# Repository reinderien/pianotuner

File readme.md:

# Custom Piano Tuner

## Environment

### apt packages

- libasound2-dev (for compilation only)
- libasound2 - underlying ALSA support
- linux-libc-dev - Linux headers for SPI

Remove pulseaudio.

Todo: move to headless mode and blow away a pile of unneeded packages.

### /boot/config.txt

```
# See https://rpf.io/configtxt
dtparam=spi=on

dtoverlay=spi0-1cs

arm_64bit=1

# todo: turn off video
```

### Audio USB device details

`dmesg`:

```
usb 1-1.2: new full-speed USB device number 3 using xhci_hcd
usb 1-1.2: New USB device found, idVendor=0d8c, idProduct=013c, bcdDevice= 1.00
usb 1-1.2: New USB device strings: Mfr=1, Product=2, SerialNumber=0
usb 1-1.2: Product: USB PnP Sound Device
usb 1-1.2: Manufacturer: C-Media Electronics Inc.      
input: C-Media Electronics Inc.       USB PnP Sound Device as /devices/platform/scb/fd500000.pcie/pci0000:00/0000:00:00.0/0000:01:00.0/usb1/1-1/1-1.2/1-1.2:1.2/0003:0D8C:013C.0001/input/input0
hid-generic 0003:0D8C:013C.0001: input,hidraw0: USB HID v1.00 Device [C-Media Electronics Inc.       USB PnP Sound Device] on usb-0000:01:00.0-1.2/input2
```

`lsusb`:

```
Bus 001 Device 003: ID 0d8c:013c C-Media Electronics, Inc. CM108 Audio Controller
```

`arecord -l`:

```
**** List of CAPTURE Hardware Devices ****
card 1: Device [USB PnP Sound Device], device 0: USB Audio [USB Audio]
  Subdevices: 1/1
  Subdevice #0: subdevice #0
```

`arecord -L`:

```
default:CARD=Device
    USB PnP Sound Device, USB Audio
    Default Audio Device
sysdefault:CARD=Device
    USB PnP Sound Device, USB Audio
    Default Audio Device
hw:CARD=Device,DEV=0
    USB PnP Sound Device, USB Audio
    Direct hardware device without any conversions
plughw:CARD=Device,DEV=0
    USB PnP Sound Device, USB Audio
    Hardware device with all software conversions
```

Examine these lines in `/usr/share/alsa/alsa.conf`; the defaults should
correspond to the correct card and device listed above:

```
defaults.ctl.card 1
defaults.pcm.card 1
defaults.pcm.device 0
defaults.pcm.subdevice 0
```

### Audio input test

```
$ arecord -D hw:CARD=Device,DEV=0 -c 1 -f S16_LE -r 48000 -d 1 -v output-test
Recording WAVE 'output-test' : Signed 16 bit Little Endian, Rate 48000 Hz, Mono
Hardware PCM card 2 'USB PnP Sound Device' device 0 subdevice 0
Its setup is:
  stream       : CAPTURE
  access       : RW_INTERLEAVED
  format       : S16_LE
  subformat    : STD
  channels     : 1
  rate         : 48000
  exact rate   : 48000 (48000/1)
  msbits       : 16
  buffer_size  : 24000
  period_size  : 6000
  period_time  : 125000
  tstamp_mode  : NONE
  tstamp_type  : MONOTONIC
  period_step  : 1
  avail_min    : 6000
  period_event : 0
  start_threshold  : 1
  stop_threshold   : 24000
  silence_threshold: 0
  silence_size : 0
  boundary     : 1572864000
  appl_ptr     : 0
  hw_ptr       : 0
```

### Verifying SPI

```
$ raspi-gpio get | grep SPI0
GPIO 9: level=0 fsel=4 alt=0 func=SPI0_MISO pull=DOWN
GPIO 10: level=0 fsel=4 alt=0 func=SPI0_MOSI pull=DOWN
GPIO 11: level=0 fsel=4 alt=0 func=SPI0_SCLK pull=DOWN
```

```
$ lsmod | grep spi
spidev                 24576  0
spi_bcm2835            24576  0
```

```
$ ls -l /dev/spi*
crw-rw---- 1 root spi 153, 0 Dec  5 17:06 /dev/spidev0.0
```

```
# First, guarantee sync; this requires at most two bytes
echo -ne "\x00\x00" > /dev/spidev0.0

# Channel 1: 1V, 205: 0b001_000_00 0b1100_1101
echo -ne "\x20\xCD" > /dev/spidev0.0

# Channel 2: 2V, 410: 0b010_000_01 0b1001_1010
echo -ne "\x41\x9A" > /dev/spidev0.0

# Channel 5: 3V, 614: 0b101_000_10 0b0110_0110
echo -ne "\xA2\x66" > /dev/spidev0.0

# Channel 4: 4V, 26, 0b100_11001
echo -ne "\x99" > /dev/spidev0.0
```

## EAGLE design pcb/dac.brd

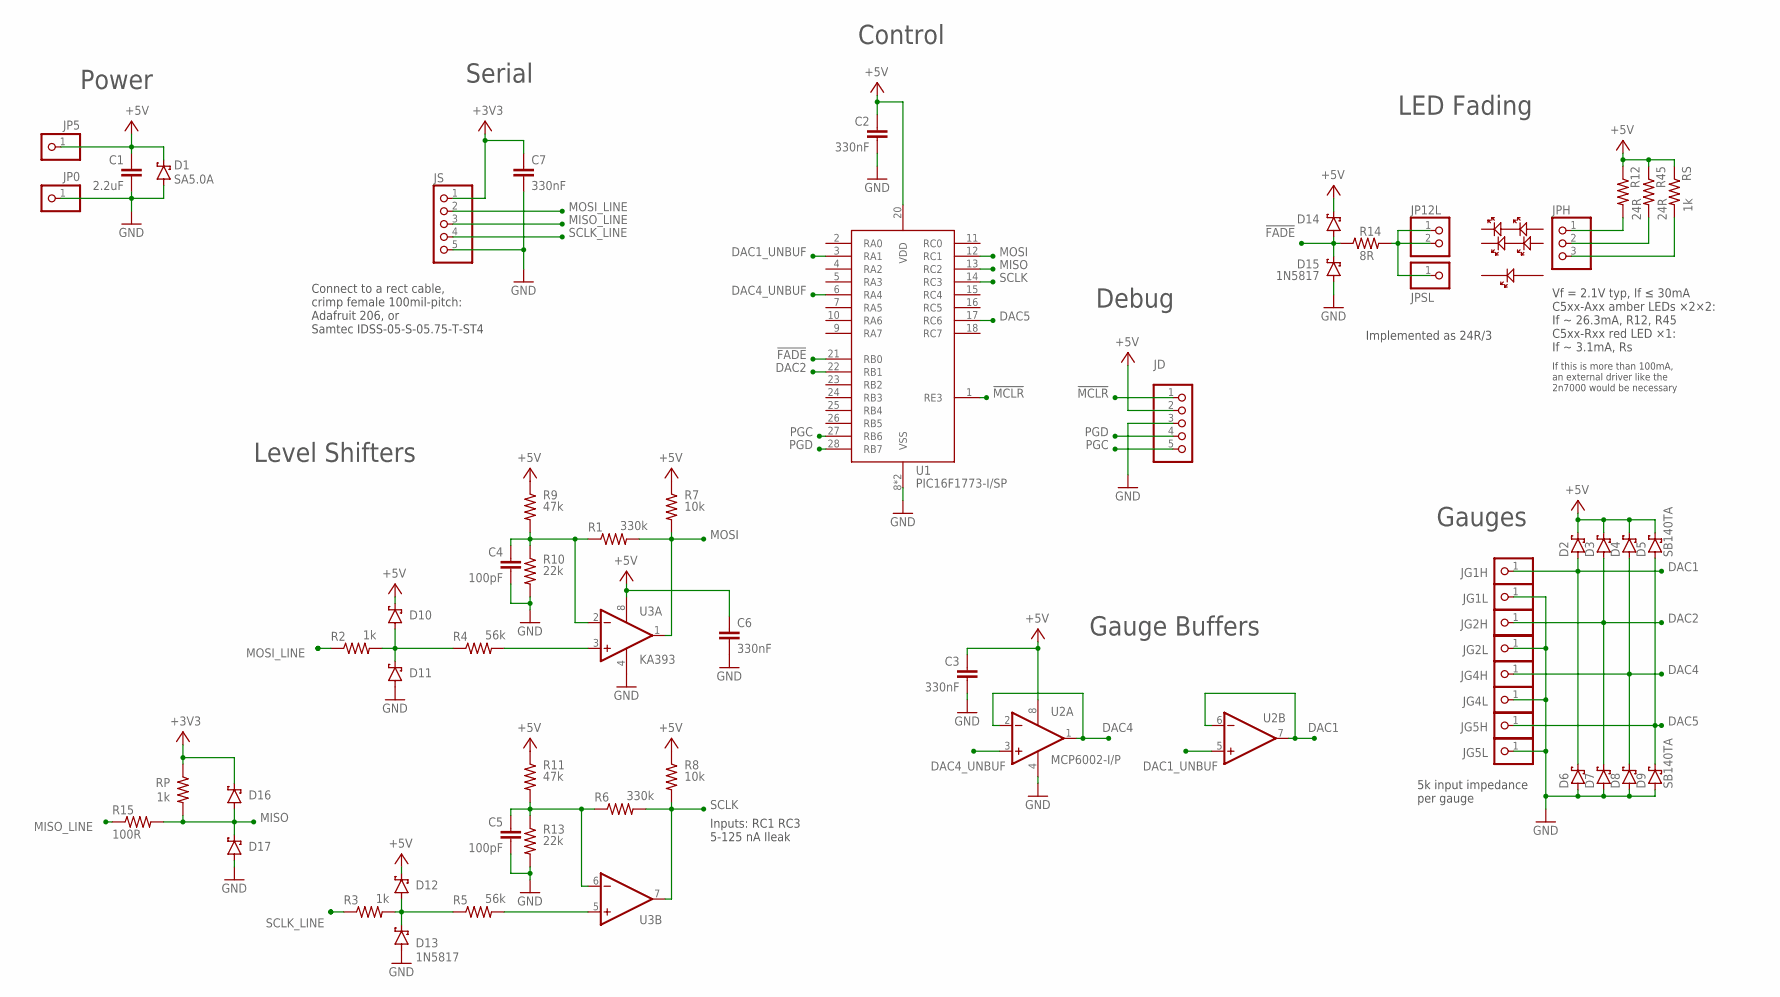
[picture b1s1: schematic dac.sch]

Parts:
C1: 2.2uF; C050-024X044
C2, C3, C6, C7: 330nF; C050-024X044
C4, C5: 100pF; C050-024X044
D1: SA5.0A; ZDIO-2.5
D2, D3, D4, D5, D6, D7, D8, D9: SB140TA; DO41-7.6
D10: 1N5817-H76; DO41-7.6
D11: 1N5817-V; ZDIO-2.5
D12, D16, D17: 1N5817-T; DO41-7.6
D13: 1N5817; DO41-10
D14, D15: 1N5817; ZDIO-2.5
JD: PINHD-1X5; 1X05
JG1H, JG1L, JG2H, JG2L, JG4H, JG4L, JG5H, JG5L: PINHD-1X1; 1X01
JP0, JP5: PINHD-1X1; 1X01
JP12L: PINHD-1X2; 1X02
JPH: PINHD-1X3; 1X03
JPSL: PINHD-1X1; 1X01
JS: PINHD-1X5; 1X05
R1, R6: 330k; 0207/2V
R2: 1k; 0204/7
R3: 1k; 0207/10
R4: 56k; 0207/10
R5: 56k; 0207/12
R7, R8: 10k; 0207/2V
R9: 47k; 0207/7
R10, R13: 22k; 0207/5V
R11: 47k; 0207/5V
R12, R45: 24R; 0207/2V
R14: 8R; 0207/15
R15: 100R; 0207/10
RP: 1k; 0207/5V
RS: 1k; 0207/2V
U1: PIC16F1773-I/SP; DIL28-3
U2: MCP6002-I/P; DIL08
U3: KA393; DIL08

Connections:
!FADE: D14.A, D15.C, R14.1, U1.21 (RB0)
!FADE_PROT: JP12L.1, JP12L.2, JPSL.1, R14.2
!MCLR: JD.1, U1.1 (RE3)
+3V3: C7.1, D16.C, JS.1, RP.1
+5V: C1.1, C2.1, C3.1, C6.1, D1.C, D2.C, D3.C, D4.C, D5.C, D10.C, D12.C, D14.C, JD.2, JP5.1, R7.1, R8.1, R9.1, R11.1, R12.1, R45.1, RS.1, U1.20 (VDD), U2.8 (V+), U3.8 (V+)
DAC1: D2.A, D6.C, JG1H.1, U2.6 (-IN), U2.7 (OUT)
DAC1_UNBUF: U1.3 (RA1), U2.5 (+IN)
DAC2: D3.A, D7.C, JG2H.1, U1.22 (RB1)
DAC4: D4.A, D8.C, JG4H.1, U2.1 (OUT), U2.2 (-IN)
DAC4_UNBUF: U1.6 (RA4), U2.3 (+IN)
DAC5: D5.A, D9.C, JG5H.1, U1.17 (RC6)
GND: C1.2, C2.2, C3.2, C4.2, C5.2, C6.2, C7.2, D1.A, D6.A, D7.A, D8.A, D9.A, D11.A, D13.A, D15.A, D17.A, JD.3, JG1L.1, JG2L.1, JG4L.1, JG5L.1, JP0.1, JS.5, R10.2, R13.2, U1.8 (VSS), U1.19 (VSS), U2.4 (V-), U3.4 (V-)
LED1: JPH.1, R12.2
LED2: JPH.2, R45.2
LEDSUP: JPH.3, RS.2
MISO: D16.A, D17.C, R15.2, RP.2, U1.13 (RC2)
MISO_LINE: JS.3, R15.1
MOSI: R1.2, R7.2, U1.12 (RC1), U3.1 (OUT)
MOSI_LINE: JS.2, R2.1
MOSI_N: C4.1, R1.1, R9.2, R10.1, U3.2 (-IN)
MOSI_P: R4.2, U3.3 (+IN)
MOSI_PROT: D10.A, D11.C, R2.2, R4.1
PGC: JD.5, U1.27 (RB6)
PGD: JD.4, U1.28 (RB7)
SCLK: R6.2, R8.2, U1.14 (RC3), U3.7 (OUT)
SCLK_LINE: JS.4, R3.1
SCLK_N: C5.1, R6.1, R11.2, R13.1, U3.6 (-IN)
SCLK_P: R5.2, U3.5 (+IN)
SCLK_PROT: D12.A, D13.C, R3.2, R5.1

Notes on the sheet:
5k input impedance per gauge
Connect to a rect cable, crimp female 100mil-pitch: Adafruit 206, or Samtec IDSS-05-S-05.75-T-ST4
Vf = 2.1V typ, If ≤ 30mA C5xx-Axx amber LEDs ×2×2: If ~ 26.3mA, R12, R45 C5xx-Rxx red LED ×1: If ~ 3.1mA, Rs
Gauges
Gauge Buffers
LED Fading
Serial
Debug
Power
Control
If this is more than 100mA, an external driver like the 2n7000 would be necessary
Inputs: RC1 RC3 5-125 nA Ileak
Level Shifters
Implemented as 24R/3

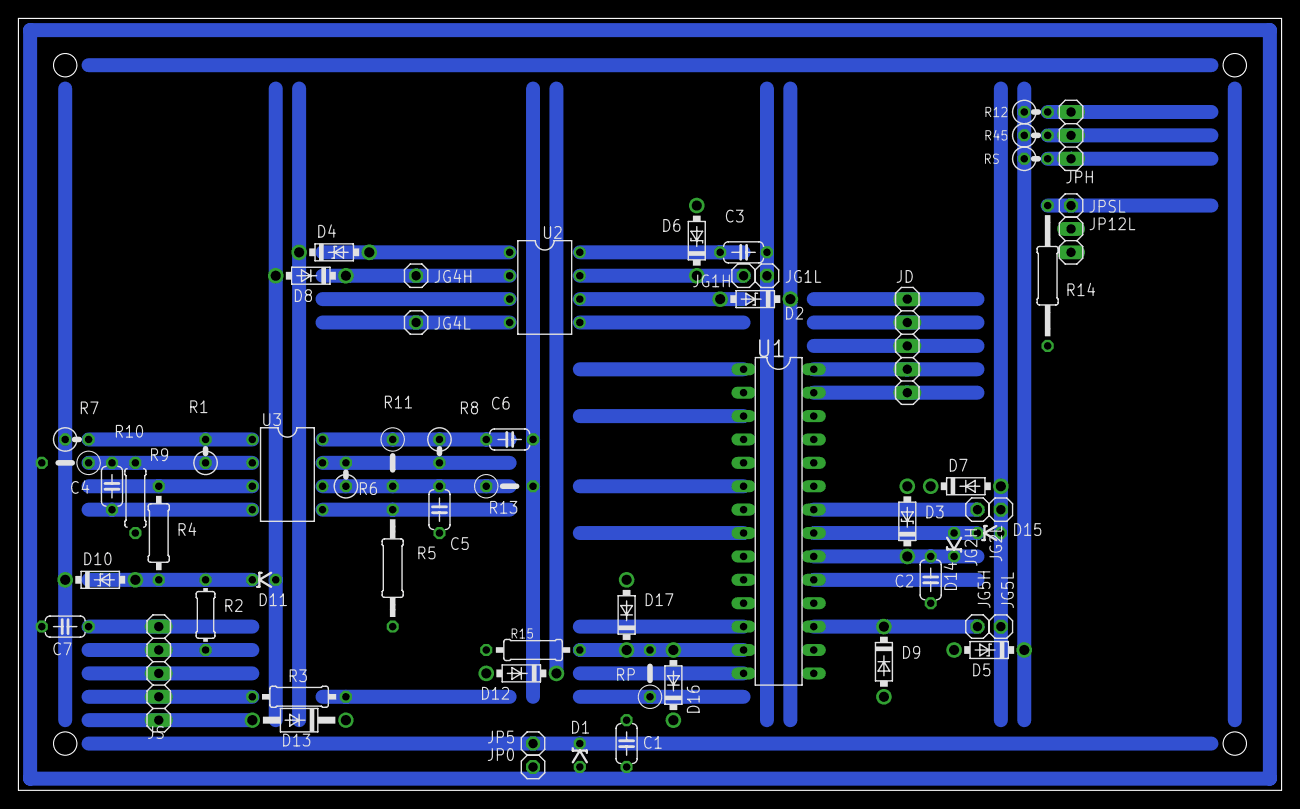
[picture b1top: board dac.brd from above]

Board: 2 copper layers, 137.2 x 83.8 mm, 60 parts (0 on the bottom side), 29 nets.

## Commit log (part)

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2015-12-20 Initial commit - successfully captures and plots
2015-12-20 Note detection
2015-12-20 Interpolate for graphing
2015-12-20 Move capture callback out to top level
2015-12-21 Working updating graph
2015-12-21 Tuning subplot
2020-10-03 Move ancient Python script to a subdirectory
2020-10-04 SDL capture (uses Alsa underneath)
2020-10-04 Rely on git for clean
2020-10-04 Output flags before build
2020-10-05 Switch to ALSA
2020-10-05 Some hardware parameter selection
2020-10-05 Drop trailing spaces; apply the hwparams
2020-10-05 Use ALSA dump feature
2020-10-05 Show skip-messages in enumeration
2020-10-05 Parametric gcc
2020-10-05 Warnings while shutting down pcm
2020-10-05 Explicitly include device number in pcm open call
2020-10-05 Explicitly reference subdevice in name; fix alloca bug
2020-10-06 Do some calculations; move to a minimum permissible sampling freq
2020-10-06 Basic capture runs
2020-10-06 Qualify some context pointers
2020-10-06 Do an initial start to avoid a first restart bump
2020-10-06 Add a control info section
2020-10-06 Describe elements
2020-10-06 Array-ize more name utilities
2020-10-06 Add sanity checks for enums
2020-10-06 Show current element values
2020-10-06 Modify AGC and gain
2020-10-06 Infinite loop; catch sigint; basic monitor
2020-10-06 Fix the double free
2020-10-07 Base volume on a fraction of max
2020-10-07 Those constants are all for open
2020-10-07 Do not care about min
2020-10-10 Basic GSL build
2020-10-10 Wrong headers for readme
2020-10-10 Greatly simplify makefile; fix Atlas include order
2020-10-10 Don't care about gcc location
2020-10-11 Support debug/release profile
2020-10-11 Reduce default verbosity of element dump
2020-10-11 Initialize max_int, though it will not matter in our case
2020-10-11 Split off frequency analysis
2020-10-11 Split out meter and dump routines
2020-10-11 Initial notes on BLAS
2020-10-12 Use default device instead of enumerating; float conversion yields all 0 so far
2020-10-12 Switch back to mmap s16; try out some BLAS which does not work
2020-10-12 Trial implementation using dot products
2020-10-12 Dot product method seems to work, 4ms
2020-10-12 Dump GSL
2020-10-12 Move to cblas notes
2020-10-12 Show frequency in dump
2020-10-12 Parametric rate
2020-10-12 Valley-to-peak algorithm
2020-10-12 Finding good thresholds is going to be tricky
2020-10-12 This space hack has to go
2020-10-12 Next is a calibration aide
2020-10-19 Empty PIC project
2020-10-20 Basic assembling, link and program
2020-10-20 Only init once
2020-10-21 Do a bunch of PIC init
2020-10-21 PPS, SPI and opamp init
2020-10-23 Initial schematic for DAC
2020-10-23 start a journal retroactively
2020-10-23 Switch to high-voltage programming
2020-10-23 More journal details - including reference to the old Google doc
2020-10-23 Some pics for the journal; not yet embedded
2020-10-23 Embed pictures and descriptions in journal
2020-10-23 Supplier correction
2020-10-25 Notes from Oct 24 on fade subprogram
2020-10-28 Yet more fade calculations
2020-10-30 Add fade circuit and a little firmware
2020-10-30 Start timer 2
2020-11-01 Simultaneous start
2020-11-24 PWM beat frequency works great; COG has trouble somehow related to input PWM duty cycle
2020-11-25 Fade works
2020-11-25 Fade-in complete - timer interrupt works
2020-11-25 Add image of fading test circuit
2020-11-26 Terminology
2020-11-26 Increase LED drive current to 13mA
2020-11-27 Protoboard layout & routing
2020-11-27 Journal entry for DAC layout
2020-11-29 Add an (untested) implementation for SPI receiver
2020-12-01 Offset null calculations
2020-12-05 Journal - SPI stuff
2020-12-05 Notes on diffusion angle and lighting
2020-12-06 Start a gauge file; drag ALSA back to working
2020-12-06 Bash test; not working on scope yet
2020-12-06 Draft SPI parent code; will not compile yet
2020-12-06 Compilation for SPI cleaned up
2020-12-07 Level shifting for Pi
2020-12-07 Continue if xor IS zero
2020-12-13 Fix up the likely source of the MSSP problem
2020-12-13 Journal entry for woodworking
2020-12-13 MISO pullup, minor cleanup
2020-12-13 Fix polarity of MSSP
2020-12-13 Add note about high driving
2020-12-13 Simulation of SPI clock Schmitt trigger
2020-12-18 Only sleep before first byte; works at 1MHz
2020-12-18 Gauge demo
2020-12-18 Fix seconds issue
2020-12-18 Disable watchdog for now
2020-12-18 Journal entry for 17th
2020-12-19 Drop FET driver for LEDs; switch to HIDRV on B0 in open-drain mode; LEDs in serial
2020-12-19 Get closer to 30mA based on a parallel approximation; parts on hand and whatnot
2020-12-20 Journal entry for the 19th
2020-12-21 Ended up using 1k for power indicator; journal entry
2020-12-22 Journal images for gauges and math notes
2020-12-22 Journal entry for the 22nd
2020-12-30 Holiday journal entry
2020-12-31 Refactoring pass; currently segfaults in matplotlib draw
2021-01-11 Re-vamp the desktop spectral analysis - running, now needs tuning view
2021-01-11 Fundamental A440 in cents
2021-01-11 Wisdom recovery, max-normalisation
2021-01-11 Multi-harmonic display shown
2021-01-11 Halfway through adding keyboard support, classify
2021-01-11 Initial note, wisdom logic fix
2021-01-11 Everything basically works
2021-01-11 Replaced all tabs with four spaces.
2021-01-11 Added mod1rd_test and vrb_test to arm/.gitignore.
2021-01-11 A first volley at reimplementing the frequency determination code.
    - Autocorrelation is now time-averaged using a VRB.
    - Nuked the old, mostly broken frequency determination code.
    - The audio capture history and autocorrelation accumulation are now managed in
    main.c. The main peak finding still occurs in freq.c. The autocorrelation
    array and sample rate are passed as inputs.
    - Autocorrelation snapshots are now saved in raw binary format. (It is actually
2021-01-11 Implemented the Virtual Ring Buffer, plus unit tests.
    It isn't a FIFO implementation, with enqueuing and dequeuing. Its purpose is
    to store the history of a stream so that any point a certain distance in the
    past or later can be accessed. It still has what is an equivalent to enqueuing,
    called advance. It also has a "past" method, for controlled access to the
    stream's past.
2021-01-11 Switched to armpl.
2021-01-11 stropts.h is deprecated. Switching to sys/ioctl.h.
2021-01-11 Added statefulness to consume() and frequency determination code, preliminary gauge value calculation code.
    Also, removed dependency on freq.h in the audio capture code. The capture
    period is now determined by a hardcoded latency. Any history that needs to be
    captured and tracked will be done so in a separate ring buffer.
2021-01-11 Turned on gauges, fixed a db<->octave mixup, adjusted POWER_THRESHOLD.
2021-01-11 Nuke MIN_LATENCY, miscellaneous cosmetics.
2021-01-11 Resolved some double gauge message sends in the state code.
2021-01-12 Saner slicing
2021-01-13 Enforce max note, add frequency display
2021-04-29 Diffused backlights
2021-04-29 That is not a bullet
2021-06-06 Do not sleep if we are out of sync
2021-06-17 Micro issue fixup, H3s for dates
2022-05-08 Update toolchain (historical)
2022-05-08 Informative labels (historical)
2022-05-08 Update pack
2022-05-08 Enable the watchdog
2024-03-31 Some manual watchdog diagnostics
2024-03-31 Remove bogus line
2024-06-01 First stab at a numerical solution to level shifter
2024-06-01 Temporarily cut out alternative parameter structures
2024-06-02 Close to a working differential_evolution sol
2024-06-02 Callback output
2024-06-02 Add bias current
2024-06-03 Add vectorisation
2024-06-03 Add continuous printing
2024-06-03 Journal entries for level shifter
2024-06-03 Add bias to high case; add pullup constraint
2024-06-30 Add more examples
2024-07-01 New layout with larger board and level shifter
2024-07-01 Final modifications to level_shifter - restore support for continuous case
2024-07-01 MISO protection network, lower capacitance values, split jumper for LEDs
2024-07-01 Replace screw terminals with more header
2024-07-01 Update pack to 1.7.242. Add debug and release configurations. Add preliminary support for psect optimisation flags. Add comments on bank values. Convert to WPU for unused inputs. ST input levels thro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
2024-07-01 Switch back from simulator to PICkit
2024-07-01 Switch to analogue for unused pins
2024-08-04 Used different protection diodes for LEDs
2024-08-05 Do not pull MISO to 5V
2024-08-10 Modernise typing
2024-08-10 More typing
2026-06-14 Halfway through a rewrite
2026-06-15 Running (not very well)
2026-06-15 Clearer comments, vertical scale for bad mic
2026-06-15 Filter tuning
2026-06-15 Tuning for actual A440
